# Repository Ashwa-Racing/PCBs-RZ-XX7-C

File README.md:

# RZ-XX7-C Electrical and PCB Designs

This repository contains the electrical design files for the Ashwa Racing
RZ-XX7-C, a 2027 combustion prototype. It covers the accelerator pedal position
sensor board (APPS), brake system plausibility device (BSPD), control unit,
interface control unit (ICU), and vehicle wiring harness.

The KiCad projects are the editable design sources. PDF drawings, PCB
manufacturing exports, and 3D models are included where available. Firmware
source and release binaries are not part of this repository.

## Design overview

| Design | Role |
| --- | --- |
| [APPS board](<./APPS-RZ-XX7-C/>) | Reads accelerator-pedal and throttle-position signals. Its schematic includes an STM32F4x1 module, analog signal conditioning, plausibility logic, relay control, and ETB-related signals. |
| [BSPD](<./BSPD-RZ-XX7-C/>) | Monitors brake-pressure, throttle-position, and brake-light-related signals. The schematic documents the plausibility, timing, reset, relay, and shutdown-circuit logic. |
| [Control Unit](<./Control Unit/>) | Provides power switching and control interfaces for the starter relay, fuel pump, electronic throttle body, radiator fan, water pump, and compressor. |
| [Interface Control Unit](<./Interface Control Unit/>) | Provides the vehicle interface electronics, including a Raspberry Pi Zero 2 W, CAN-FD controller and transceiver, IMU connections, and power/control circuitry for the display and auxiliary lighting. |
| [Harness](<./Harness-RZ-XX7-C/>) | Documents vehicle wiring and connectors between the engine-management system, boards, sensors, actuators, display, and vehicle systems. |

These descriptions summarize the design files; consult the schematics and
harness drawing for pin assignments, circuit details, and connector wiring.

## Repository contents

Each board folder contains a KiCad schematic (`.kicad_sch`), PCB layout
(`.kicad_pcb`), project settings (`.kicad_pro`), and a plotted schematic PDF.
The harness folder contains the corresponding wiring schematic, PCB document,
and PDF drawing.

| Folder | Design documents | Additional files |
| --- | --- | --- |
| [APPS-RZ-XX7-C](<./APPS-RZ-XX7-C/>) | [Schematic PDF](<./APPS-RZ-XX7-C/APPS-RZ-XX7-C%20Schematic%20PDF.pdf>) | [Gerbers and drill file](<./APPS-RZ-XX7-C/Gerbers/>), [3D model](<./APPS-RZ-XX7-C/APPS-RZ-XX7-C.step>) |
| [BSPD-RZ-XX7-C](<./BSPD-RZ-XX7-C/>) | [Schematic PDF](<./BSPD-RZ-XX7-C/BSPD-RZ-XX7-C%20Schematic%20PDF.pdf>) | [Gerbers and drill file](<./BSPD-RZ-XX7-C/Gerbers/>), [3D model](<./BSPD-RZ-XX7-C/BSPD-RZ-XX7-C.step>) |
| [Control Unit](<./Control Unit/>) | [Schematic PDF](<./Control%20Unit/Control%20Unit%20Schematic%20PDF.pdf>) | [Gerbers and drill file](<./Control%20Unit/Gerbers/>), [3D model](<./Control%20Unit/Control%20Unit.step>) |
| [Interface Control Unit](<./Interface Control Unit/>) | [Schematic PDF](<./Interface%20Control%20Unit/Interface%20Control%20Unit%20Schematic%20PDF.pdf>) | [Gerbers and drill file](<./Interface%20Control%20Unit/Gerbers/>), [ICU and display STEP archive](<./Interface%20Control%20Unit/ICU%20+%20Display%20V2%20STEP.zip>), [ICU STEP archive](<./Interface%20Control%20Unit/RZ-XX7-C%20ICU%20STEP.zip>) |
| [Harness-RZ-XX7-C](<./Harness-RZ-XX7-C/>) | [Harness PDF](<./Harness-RZ-XX7-C/Harness-RZ-XX7-C%20PDF.pdf>) | Reference manuals and wiring diagrams are in [Datasheets](<./Harness-RZ-XX7-C/Datasheets/>) |

The Gerber folders contain the copper, solder-mask, paste, silkscreen, and
board-outline layers, along with Excellon drill data. A Gerber set is currently
present for APPS, BSPD, Control Unit, and ICU; no harness Gerber export is
included.

The ICU folder also contains power-supply analysis documents in `Documents/`
and local KiCad symbol and footprint libraries alongside several projects.
Keep those libraries with their projects when moving or editing the designs;
KiCad may need their library paths configured on another machine.

## Opening and using the designs

1. Install KiCad and open a project's `.kicad_pro` file, or open its schematic
   or PCB file directly.
2. If KiCad reports missing symbols or footprints, configure the project's
   local libraries. Several custom libraries are stored in the relevant
   project folders.
3. Review the schematic and PCB together before making changes. Use the
   checked-in PDFs for quick reference; the KiCad files remain the editable
   source.
4. For fabrication, review the Gerber and drill files in a Gerber viewer and
   confirm the board revision and fabrication requirements before sending
   them to a manufacturer. Regenerate the exports from the KiCad source after
   changing a design.

The Gerber file headers identify KiCad 10.0.6 as the export version. KiCad
projects and generated manufacturing files should be checked together when
preparing a new release.

## Firmware status

- [ ] Upload the updated firmware to the target hardware.

Firmware source and binaries are not stored here, so this repository does not
provide firmware build or upload instructions.

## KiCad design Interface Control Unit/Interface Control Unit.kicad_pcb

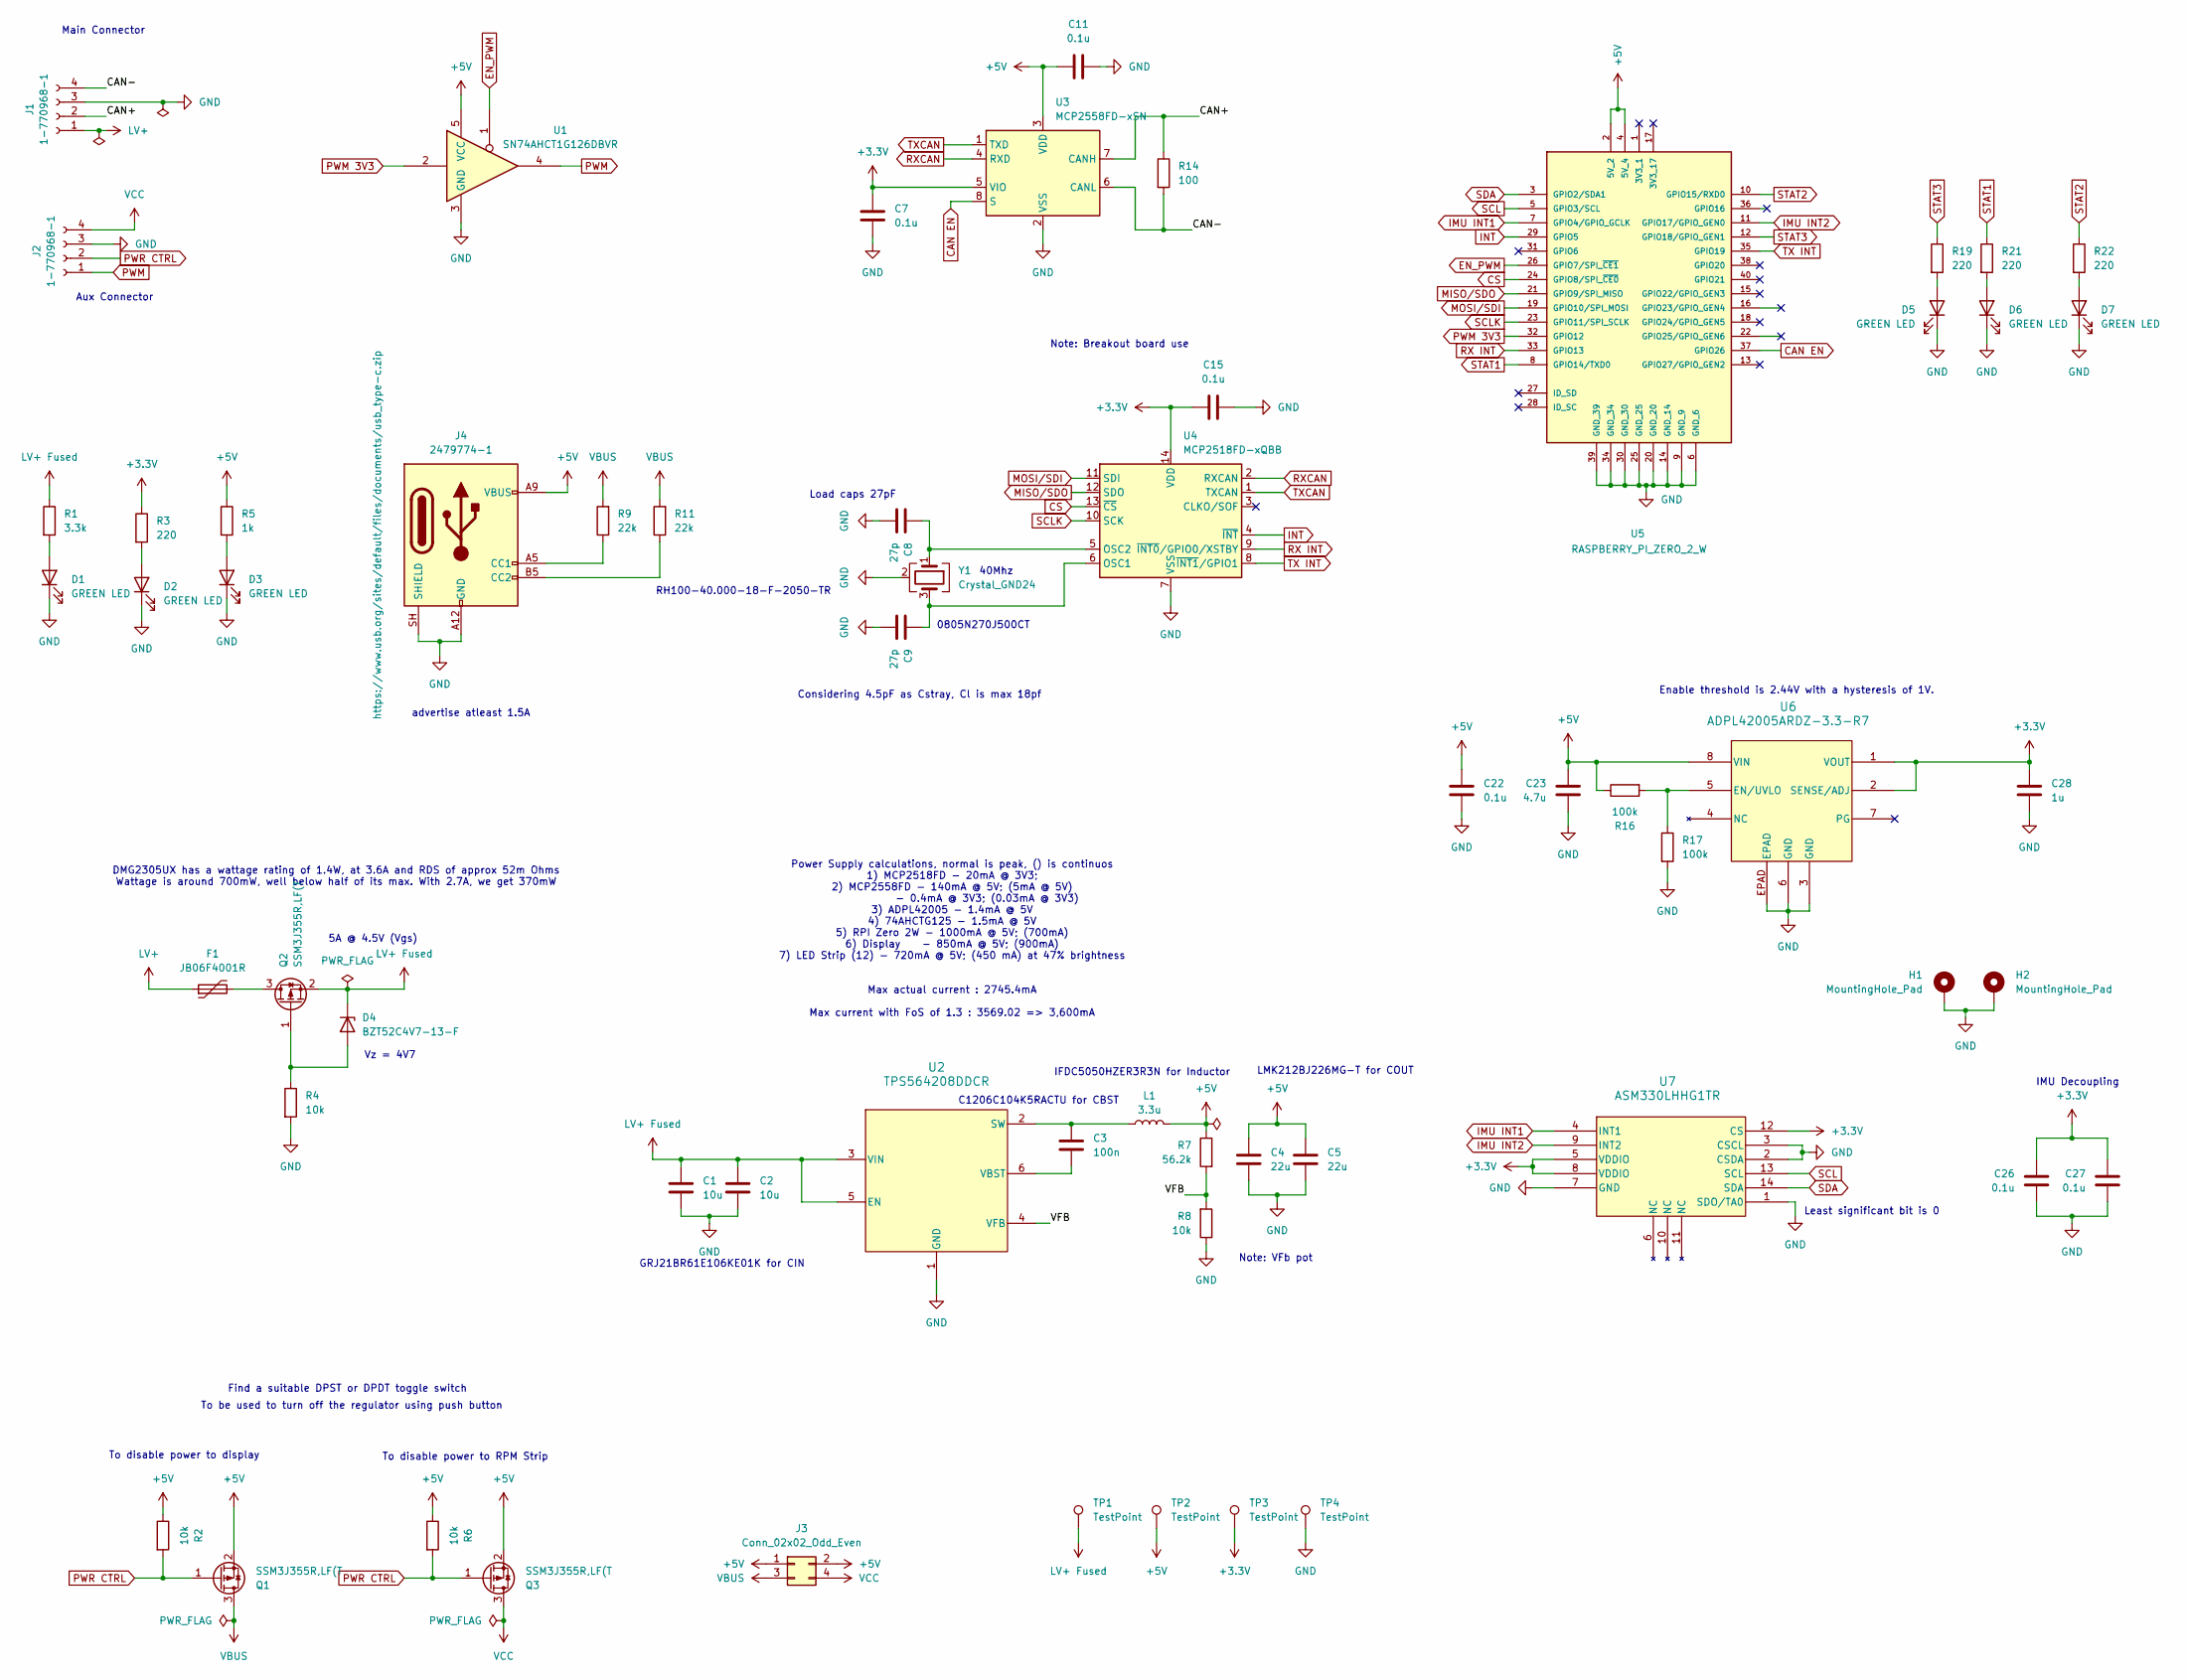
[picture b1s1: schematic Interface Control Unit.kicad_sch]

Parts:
C1, C2: 10u; C_0805_2012Metric_Pad1.18x1.45mm_HandSolder
C3: 100n; C_1206_3216Metric_Pad1.33x1.80mm_HandSolder
C4, C5: 22u; C_0805_2012Metric_Pad1.18x1.45mm_HandSolder
C7, C11, C15, C22, C26, C27: 0.1u; C_1206_3216Metric_Pad1.33x1.80mm_HandSolder
C8, C9: 27p; C_0805_2012Metric_Pad1.18x1.45mm_HandSolder
C23: 4.7u; C_1206_3216Metric_Pad1.33x1.80mm_HandSolder
C28: 1u; C_1206_3216Metric_Pad1.33x1.80mm_HandSolder
D1, D2, D3, D5, D6, D7: GREEN LED; LED_1206_3216Metric_Pad1.42x1.75mm_HandSolder
D4: BZT52C4V7-13-F; D_SOD-123F
F1: JB06F4001R; Fuse_0603_1608Metric_Pad1.05x0.95mm_HandSolder
H1, H2: MountingHole_Pad; MountingHole_2.7mm_M2.5_ISO7380_Pad
J1, J2: 1-770968-1; CONN4_1-770968-1_TEC
J3: Conn_02x02_Odd_Even; PinHeader_2x02_P2.54mm_Vertical
J4: 2479774-1; USB_C_Receptacle_GCT_USB4125-xx-x-0190_6P_TopMnt_Horizontal
L1: 3.3u; L_Vishay_IHLP-5050
Q1, Q2, Q3: SSM3J355R,LF(T; SOTFL95P240X88-3N
R1: 3.3k; R_1206_3216Metric_Pad1.30x1.75mm_HandSolder
R2, R4, R6: 10k; R_1206_3216Metric_Pad1.30x1.75mm_HandSolder
R3, R19, R21, R22: 220; R_1206_3216Metric_Pad1.30x1.75mm_HandSolder
R5: 1k; R_1206_3216Metric_Pad1.30x1.75mm_HandSolder
R7: 56.2k; R_0805_2012Metric_Pad1.20x1.40mm_HandSolder
R8: 10k; R_0805_2012Metric_Pad1.20x1.40mm_HandSolder
R9, R11: 22k; R_1206_3216Metric_Pad1.30x1.75mm_HandSolder
R14: 100; R_1206_3216Metric_Pad1.30x1.75mm_HandSolder
R16, R17: 100k; R_1206_3216Metric_Pad1.30x1.75mm_HandSolder
TP1, TP2, TP3, TP4: TestPoint; TestPoint_Pad_D2.0mm
U1: SN74AHCT1G126DBVR; SOT-23-5
U2: TPS564208DDCR; DDC0006A_M
U3: MCP2558FD-xSN; SOIC-8_3.9x4.9mm_P1.27mm
U4: MCP2518FD-xQBB; SOIC-14_3.9x8.7mm_P1.27mm
U5: RASPBERRY_PI_ZERO_2_W; Raspberry Pi Zero 2WH; PARTREV April 2024
U6: ADPL42005ARDZ-3.3-R7; RD-8-1_ADI-M
U7: ASM330LHHG1TR; LGA14L_2P5X3_STM-M
Y1: Crystal_GND24; Crystal_SMD_3225-4Pin_3.2x2.5mm

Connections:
+3.3V: C7.1, C15.1, C26.1, C27.1, C28.1, R3.1, TP3.1 (1_1), U3.5 (VIO), U4.14 (VDD), U6.1 (VOUT), U6.2 (SENSE/ADJ), U7.5 (VDDIO), U7.8 (VDDIO), U7.12 (CS)
+5V: C4.1, C5.1, C11.1, C22.1, C23.1, J3.1, J3.2, J4.A9 (VBUS), J4.B9 (VBUS), L1.2, Q1.2 (S), Q3.2 (S), R2.1, R5.1, R6.1, R7.1, R16.1, TP2.1 (1_1), U1.5 (VCC), U3.3 (VDD), U5.2 (5V_2), U5.4 (5V_4), U6.8 (VIN)
/CAN+: J1.2, R14.1, U3.7 (CANH)
/CAN-: J1.4, R14.2, U3.6 (CANL)
/VFB: R7.2, R8.2, U2.4 (VFB)
CAN EN: U3.8 (S), U5.37 (GPIO26)
CS: U4.13 (~CS), U5.24 (GPIO8/SPI_~CE0)
EN_PWM: U1.1, U5.26 (GPIO7/SPI_~CE1)
GND: C1.2, C2.2, C4.2, C5.2, C7.2, C8.2, C9.2, C11.2, C15.2, C22.2, C23.2, C26.2, C27.2, C28.2, D1.1 (K), D2.1 (K), D3.1 (K), D5.1 (K), D6.1 (K), D7.1 (K), H1.1 (1_1), H2.1 (1_1), J1.3, J2.3, J4.A12 (GND), J4.B12 (GND), J4.SH (SHIELD), R4.2, R8.1, R17.2, TP4.1 (1_1), U1.3 (GND), U2.1 (GND), U3.2 (VSS), U4.7 (VSS), U4.15 (VSS), U5.6 (GND_6), U5.9 (GND_9), U5.14 (GND_14), U5.20 (GND_20), U5.25 (GND_25), U5.30 (GND_30), U5.34 (GND_34), U5.39 (GND_39), U6.3 (GND), U6.6 (GND), U6.EPAD, U7.1 (SDO/TA0), U7.2 (CSDA), U7.3 (CSCL), U7.7 (GND), Y1.2 (G), Y1.4 (G)
IMU INT1: U5.7 (GPIO4/GPIO_GCLK), U7.4 (INT1)
IMU INT2: U5.11 (GPIO17/GPIO_GEN0), U7.9 (INT2)
INT: U4.4 (~INT), U5.29 (GPIO5)
LV+: F1.1, J1.1
LV+ Fused: C1.1, C2.1, D4.1 (K), Q2.2 (S), R1.1, TP1.1 (1_1), U2.3 (VIN), U2.5 (EN)
MISO/SDO: U4.12 (SDO), U5.21 (GPIO9/SPI_MISO)
MOSI/SDI: U4.11 (SDI), U5.19 (GPIO10/SPI_MOSI)
unnamed: D1.2 (A), R1.2
unnamed: D2.2 (A), R3.2
unnamed: D3.2 (A), R5.2
unnamed: D4.2 (A), Q2.1 (G), R4.1
unnamed: D5.2 (A), R19.2
unnamed: D6.2 (A), R21.2
unnamed: D7.2 (A), R22.2
unnamed: J4.A5 (CC1), R9.1
unnamed: J4.B5 (CC2), R11.1
unnamed: F1.2, Q2.3 (D)
unnamed: C3.1, L1.1, U2.2 (SW)
unnamed: C3.2, U2.6 (VBST)
unnamed: C9.1, U4.6 (OSC1), Y1.3
unnamed: C8.1, U4.5 (OSC2), Y1.1
unnamed: R16.2, R17.1, U6.5 (EN/UVLO)
PWM: J2.1, U1.4
PWM 3V3: U1.2, U5.32 (GPIO12)
PWR CTRL: J2.2, Q1.1 (G), Q3.1 (G), R2.2, R6.2
RX INT: U4.9 (~INT0/GPIO0/XSTBY), U5.33 (GPIO13)
RXCAN: U3.4 (RXD), U4.2 (RXCAN)
SCL: U5.5 (GPIO3/SCL), U7.13 (SCL)
SCLK: U4.10 (SCK), U5.23 (GPIO11/SPI_SCLK)
SDA: U5.3 (GPIO2/SDA1), U7.14 (SDA)
STAT1: R21.1, U5.8 (GPIO14/TXD0)
STAT2: R22.1, U5.10 (GPIO15/RXD0)
STAT3: R19.1, U5.12 (GPIO18/GPIO_GEN1)
TX INT: U4.8 (~INT1/GPIO1), U5.35 (GPIO19)
TXCAN: U3.1 (TXD), U4.1 (TXCAN)
VBUS: J3.3, Q1.3 (D), R9.2, R11.2
VCC: J2.4, J3.4, Q3.3 (D)

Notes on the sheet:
Enable threshold is 2.44V with a hysteresis of 1V.
IFDC5050HZER3R3N for Inductor
Power Supply calculations, normal is peak, () is continuos 1) MCP2518FD - 20mA @ 3V3; 2) MCP2558FD - 140mA @ 5V; (5mA @ 5V) - 0.4mA @ 3V3; (0.03mA @ 3V3) 3) ADPL42005 - 1.4mA @ 5V 4) 74AHCTG125 - 1.5mA @ 5V 5) RPI Zero 2W - 1000mA @ 5V; (700mA) 6) Display - 850mA @ 5V; (900mA) 7) LED Strip (12) - 7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
To disable power to display
To be used to turn off the regulator using push button
0805N270J500CT
Considering 4.5pF as Cstray, Cl is max 18pf
Main Connector
40Mhz
Note: Breakout board use
Load caps 27pF
Note: VFb pot
C1206C104K5RACTU for CBST
Least significant bit is 0
advertise atleast 1.5A
To disable power to RPM Strip
Aux Connector
LMK212BJ226MG-T for COUT
DMG2305UX has a wattage rating of 1.4W, at 3.6A and RDS of approx 52m Ohms Wattage is around 700mW, well below half of its max. With 2.7A, we get 370mW
IMU Decoupling
5A @ 4.5V (Vgs)
RH100-40.000-18-F-2050-TR
GRJ21BR61E106KE01K for CIN
Find a suitable DPST or DPDT toggle switch
Vz = 4V7

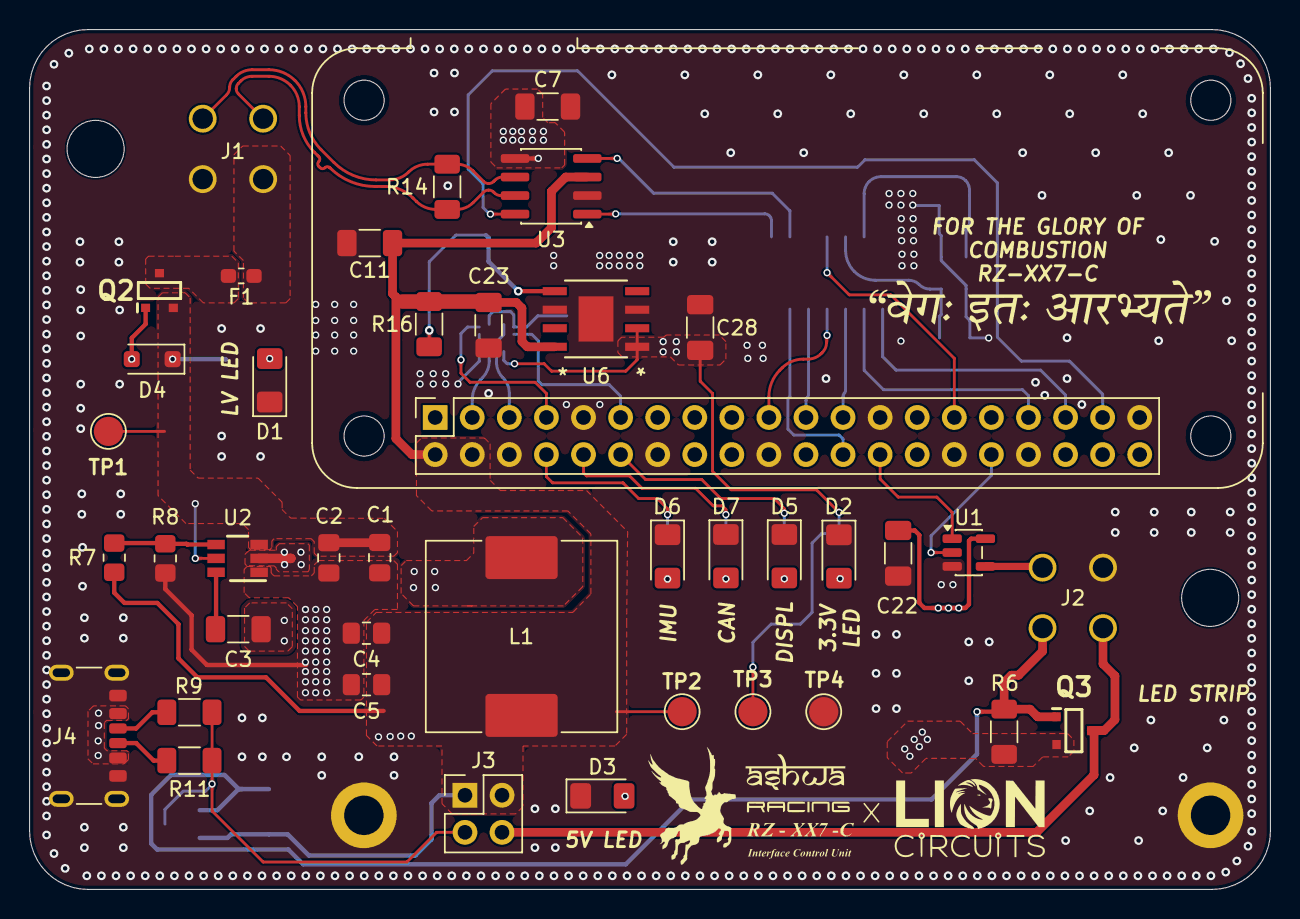
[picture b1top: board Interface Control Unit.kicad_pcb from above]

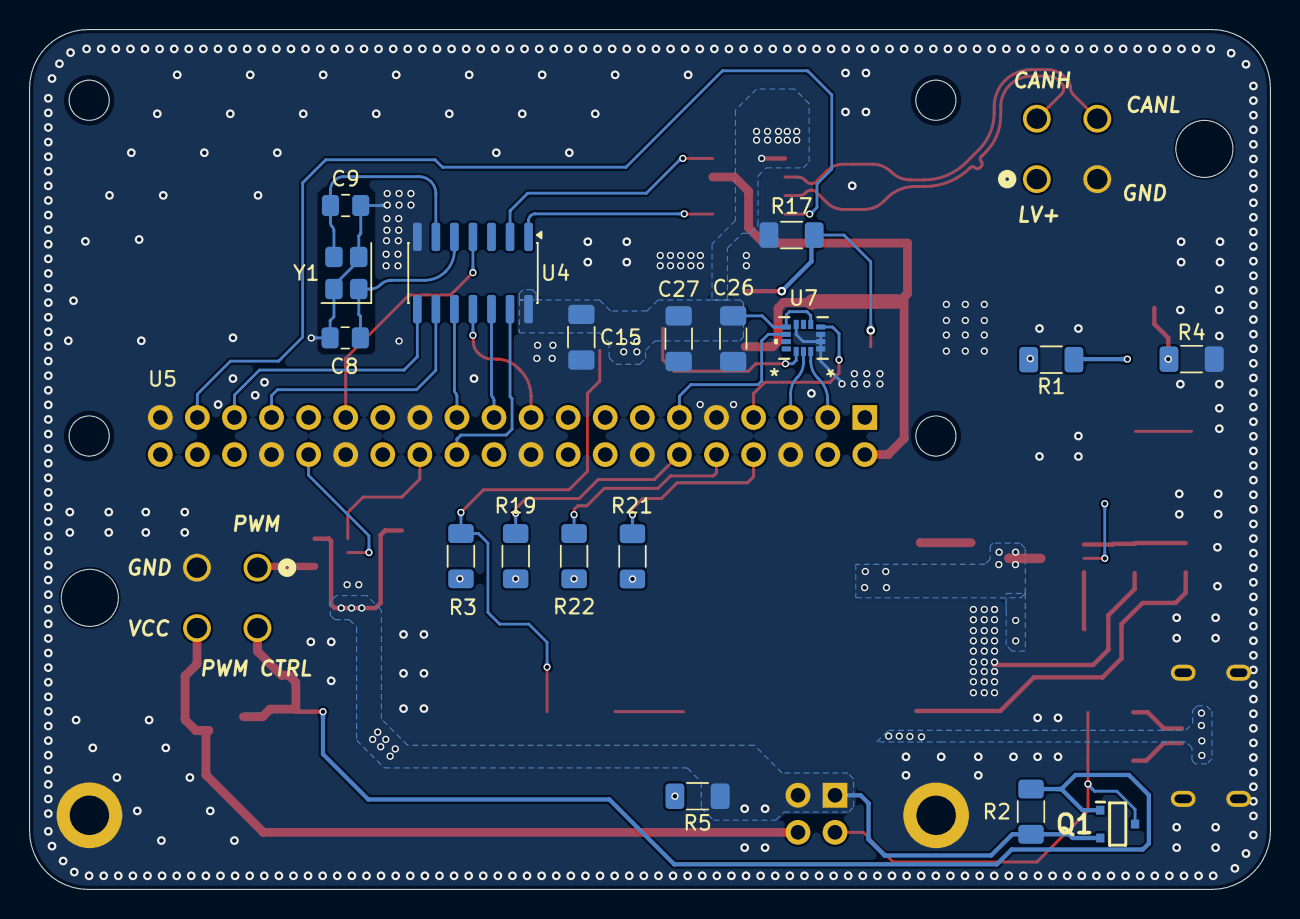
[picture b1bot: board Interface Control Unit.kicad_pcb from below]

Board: 2 copper layers, 85.0 x 58.9 mm, 61 parts (18 on the bottom side), 46 nets.

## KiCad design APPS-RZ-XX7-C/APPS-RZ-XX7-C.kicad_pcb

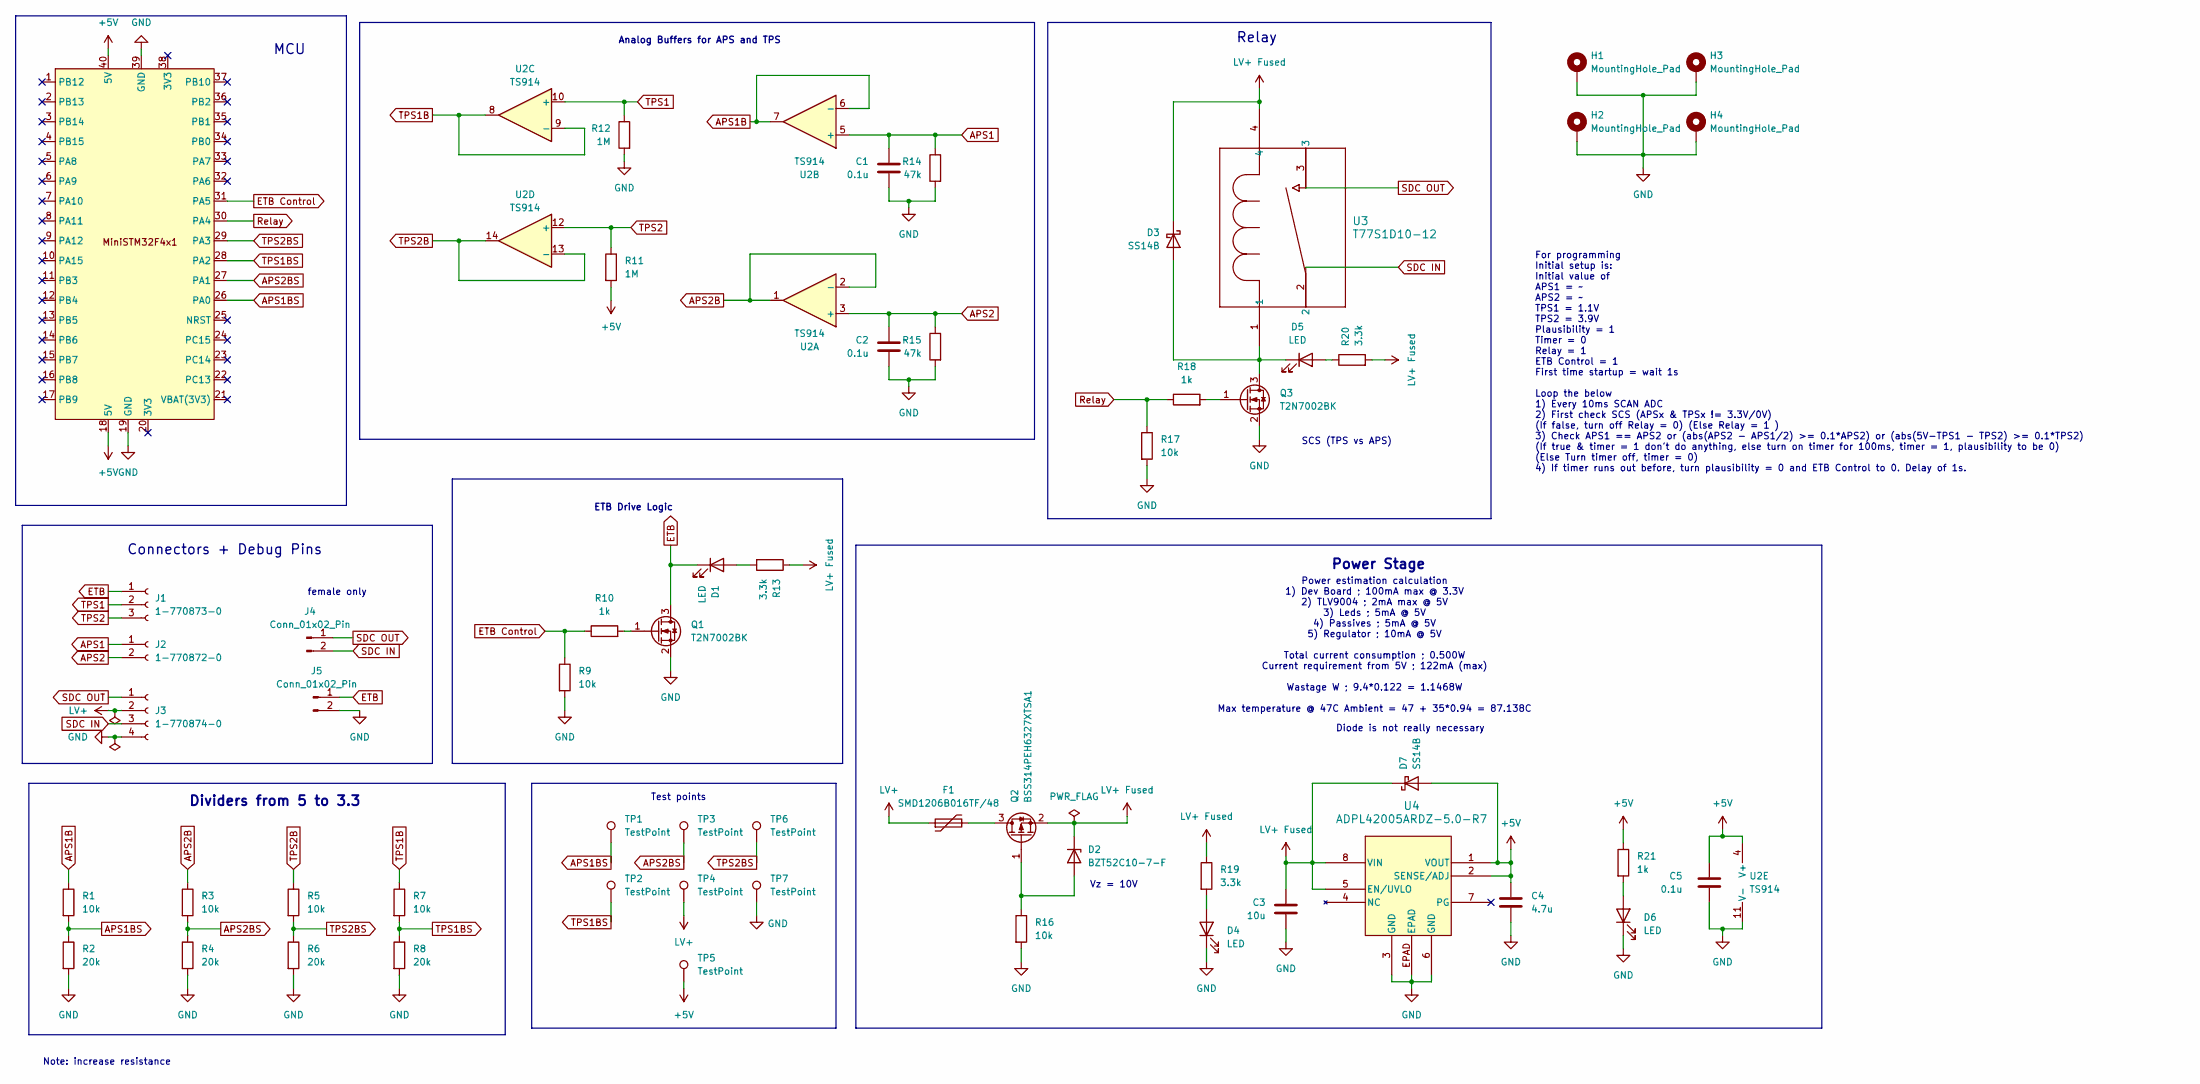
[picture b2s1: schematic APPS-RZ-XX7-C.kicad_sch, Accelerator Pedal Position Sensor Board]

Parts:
C1, C2, C5: 0.1u; C_1206_3216Metric_Pad1.33x1.80mm_HandSolder
C3: 10u; C_1206_3216Metric_Pad1.33x1.80mm_HandSolder
C4: 4.7u; C_1206_3216Metric_Pad1.33x1.80mm_HandSolder
D1, D4, D5, D6: LED; LED_1206_3216Metric_Pad1.42x1.75mm_HandSolder
D2: BZT52C10-7-F; D_SOD-123F
D3, D7: SS14B; D_SMB
F1: SMD1206B016TF/48; Fuse_1206_3216Metric_Pad1.42x1.75mm_HandSolder
H1, H2, H3, H4: MountingHole_Pad; MountingHole_4.3mm_M4_ISO7380_Pad
J1: 1-770873-0; CON3_1X3_P163_VMNL-1MTG_TYC
J2: 1-770872-0; CON2_1X2_P163_VMNL-1MTG_TYC
J3: 1-770874-0; CONN4_1-770874-0_TEC
J4, J5: Conn_01x02_Pin; PinHeader_1x02_P2.54mm_Vertical
Q1, Q3: T2N7002BK; SOT-23
Q2: BSS314PEH6327XTSA1; SOT-23
R1, R3, R5, R7, R9, R16, R17: 10k; R_1206_3216Metric_Pad1.30x1.75mm_HandSolder
R2, R4, R6, R8: 20k; R_1206_3216Metric_Pad1.30x1.75mm_HandSolder
R10, R18, R21: 1k; R_1206_3216Metric_Pad1.30x1.75mm_HandSolder
R11, R12: 1M; R_1206_3216Metric_Pad1.30x1.75mm_HandSolder
R13, R19, R20: 3.3k; R_1206_3216Metric_Pad1.30x1.75mm_HandSolder
R14, R15: 47k; R_1206_3216Metric_Pad1.30x1.75mm_HandSolder
TP1, TP2, TP3, TP4, TP5, TP6, TP7: TestPoint; TestPoint_Pad_D2.0mm
U1: MiniSTM32F4x1; Mini_F4X1_STM32
U2: TS914; SOIC-14_3.9x8.7mm_P1.27mm
U3: T77S1D10-12; RELAY4-402X717_575
U4: ADPL42005ARDZ-5.0-R7; RD-8-1_ADI

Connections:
+5V: C4.1, C5.1, D7.2 (A), R11.2, R21.1, TP5.1 (1_1), U1.18 (5V), U1.40 (5V), U2.4 (V+), U4.1 (VOUT), U4.2 (SENSE/ADJ)
APS1: C1.1, J2.1, R14.1, U2.5 (+)
APS1B: R1.1, U2.6 (-), U2.7
APS1BS: R1.2, R2.1, TP1.1 (1_1), U1.26 (PA0)
APS2: C2.1, J2.2, R15.1, U2.3 (+)
APS2B: R3.1, U2.1, U2.2 (-)
APS2BS: R3.2, R4.1, TP3.1 (1_1), U1.27 (PA1)
ETB: D1.1 (K), J1.1, J5.1, Q1.3 (D)
ETB Control: R9.1, R10.1, U1.31 (PA5)
GND: C1.2, C2.2, C3.2, C4.2, C5.2, D4.1 (K), D6.1 (K), H1.1 (1_1), H2.1 (1_1), H3.1 (1_1), H4.1 (1_1), J3.4, J5.2, Q1.2 (S), Q3.2 (S), R2.2, R4.2, R6.2, R8.2, R9.2, R12.2, R14.2, R15.2, R16.2, R17.2, TP7.1 (1_1), U1.19 (GND), U1.39 (GND), U2.11 (V-), U4.3 (GND), U4.6 (GND), U4.EPAD
LV+: F1.1, J3.2, TP4.1 (1_1)
LV+ Fused: C3.1, D2.1 (K), D3.1 (K), D7.1 (K), Q2.2 (S), R13.1, R19.1, R20.2, U3.4, U4.5 (EN/UVLO), U4.8 (VIN)
unnamed: D1.2 (A), R13.2
unnamed: D2.2 (A), Q2.1 (G), R16.1
unnamed: D3.2 (A), D5.1 (K), Q3.3 (D), U3.1
unnamed: D4.2 (A), R19.2
unnamed: D5.2 (A), R20.1
unnamed: D6.2 (A), R21.2
unnamed: Q1.1 (G), R10.2
unnamed: F1.2, Q2.3 (D)
unnamed: Q3.1 (G), R18.2
Relay: R17.1, R18.1, U1.30 (PA4)
SDC IN: J3.3, J4.2, U3.2
SDC OUT: J3.1, J4.1, U3.3
TPS1: J1.2, R12.1, U2.10 (+)
TPS1B: R7.1, U2.8, U2.9 (-)
TPS1BS: R7.2, R8.1, TP2.1 (1_1), U1.28 (PA2)
TPS2: J1.3, R11.1, U2.12 (+)
TPS2B: R5.1, U2.13 (-), U2.14
TPS2BS: R5.2, R6.1, TP6.1 (1_1), U1.29 (PA3)

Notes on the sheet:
female only
For programming Initial setup is: Initial value of APS1 = ~ APS2 = ~ TPS1 = 1.1V TPS2 = 3.9V Plausibility = 1 Timer = 0 Relay = 1 ETB Control = 1 First time startup = wait 1s Loop the below 1) Every 10ms SCAN ADC 2) First check SCS (APSx & TPSx != 3.3V/0V) (If false, turn off Relay = 0) (Else Relay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
Relay
Power Stage
Note: increase resistance
SCS (TPS vs APS)
MCU
Vz = 10V
Connectors + Debug Pins
Dividers from 5 to 3.3
Test points
Power estimation calculation 1) Dev Board ; 100mA max @ 3.3V 2) TLV9004 ; 2mA max @ 5V 3) Leds ; 5mA @ 5V 4) Passives ; 5mA @ 5V 5) Regulator ; 10mA @ 5V Total current consumption ; 0.500W Current requirement from 5V ; 122mA (max) Wastage W ; 9.4*0.122 = 1.1468W Max temperature @ 47C Ambient = 47 +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
ETB Drive Logic
Analog Buffers for APS and TPS
Diode is not really necessary

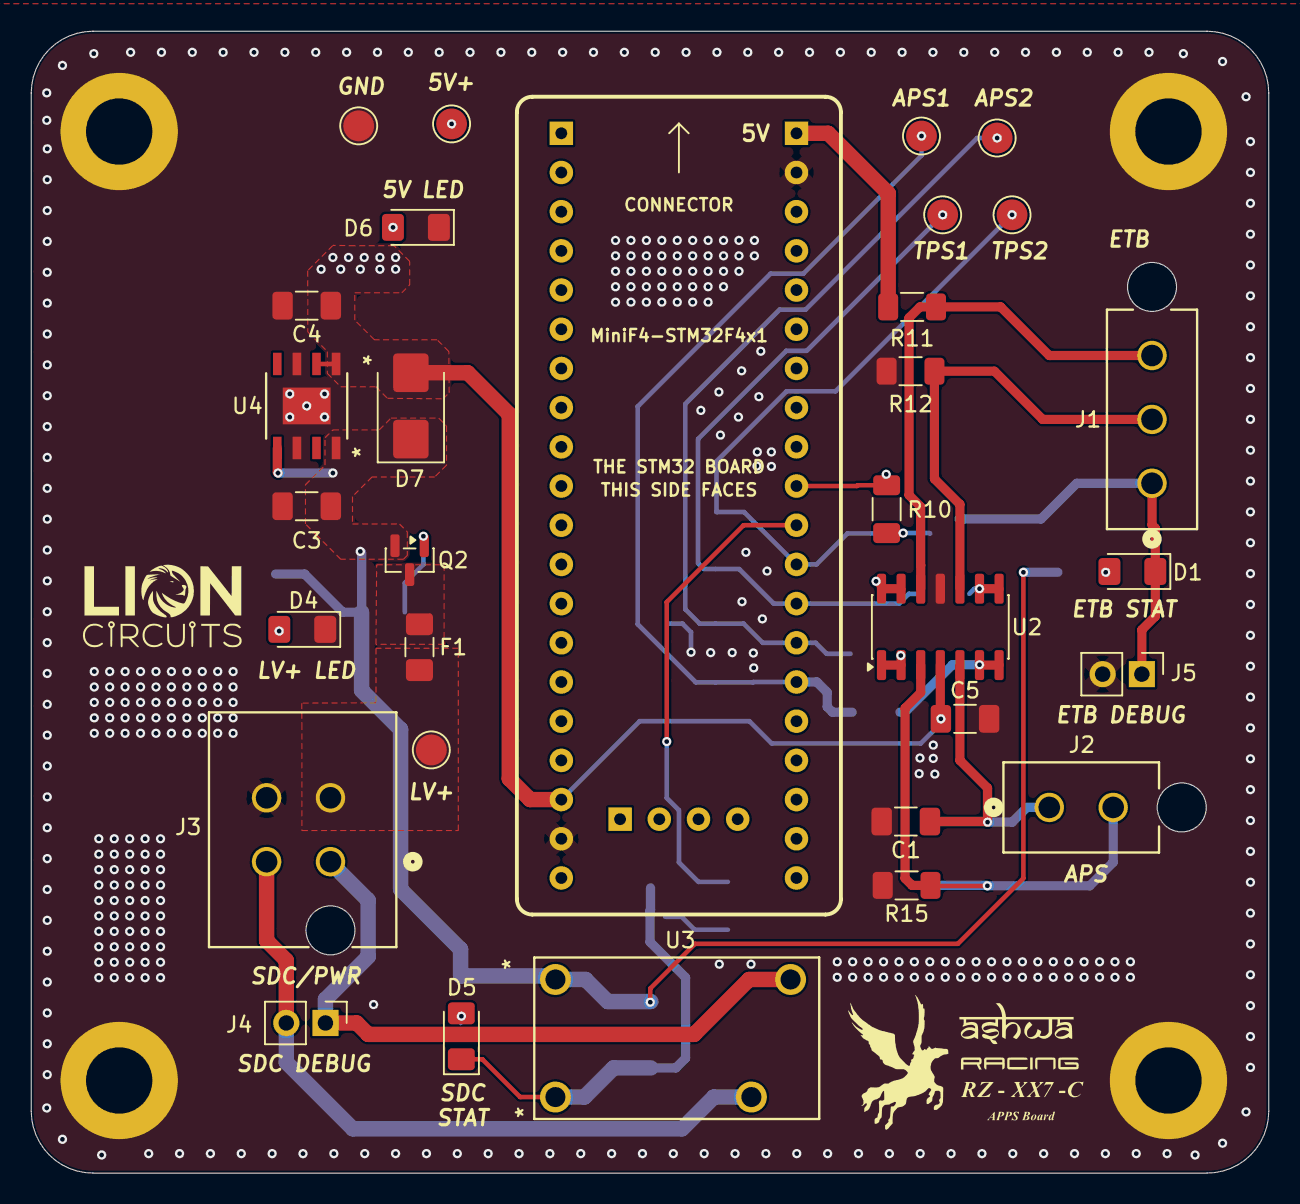
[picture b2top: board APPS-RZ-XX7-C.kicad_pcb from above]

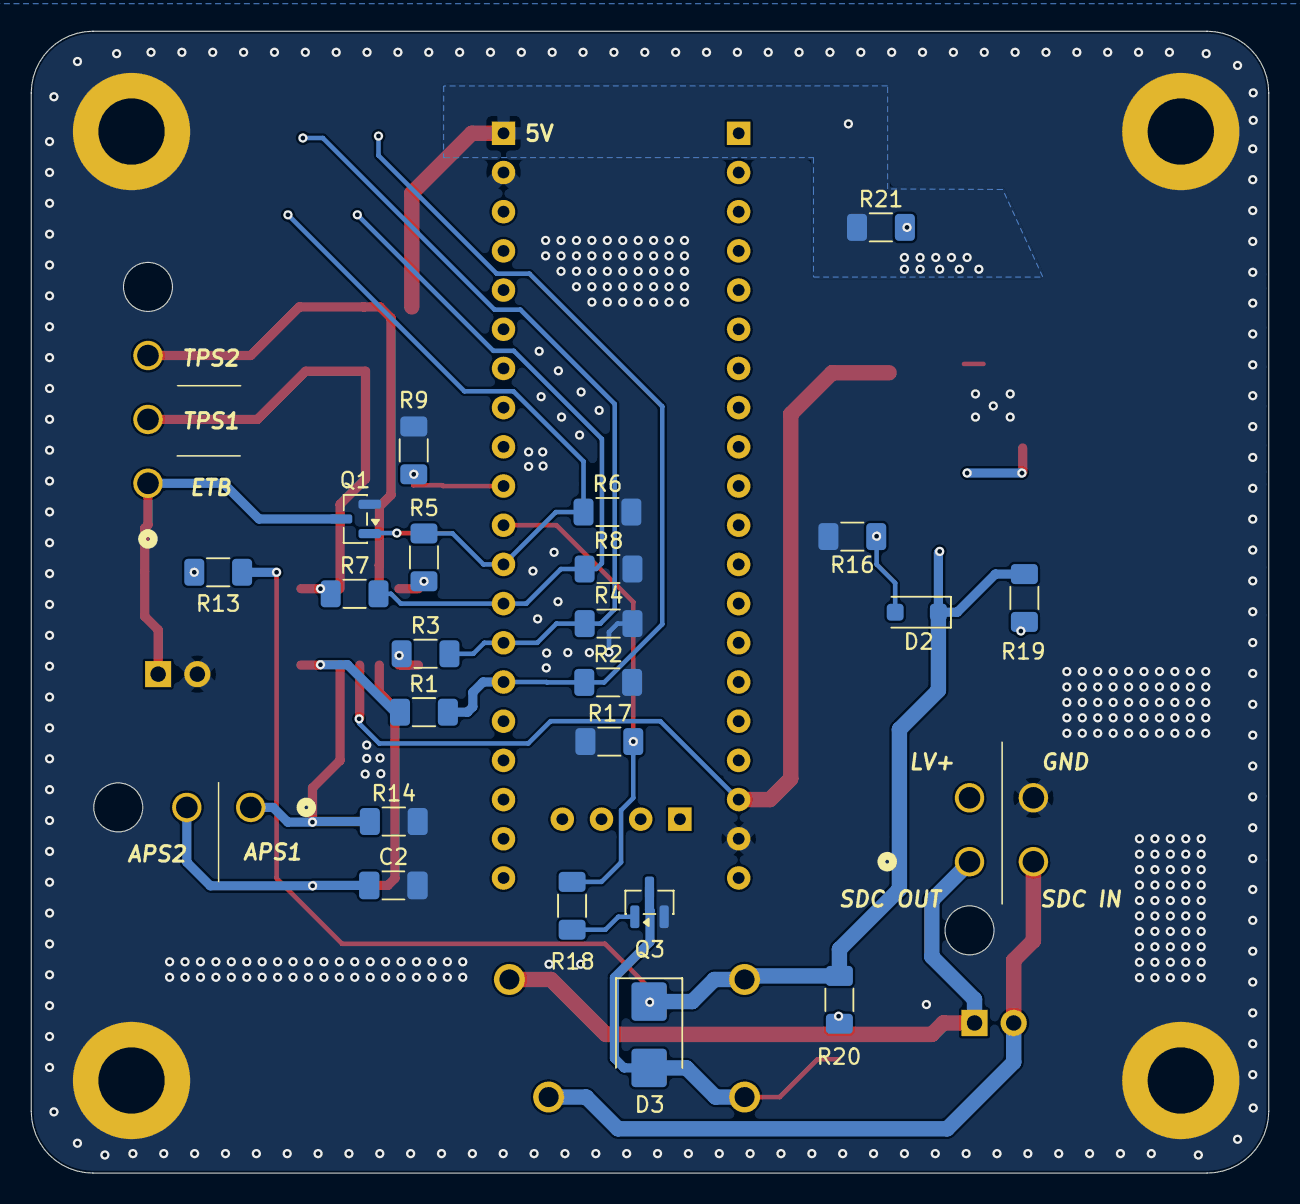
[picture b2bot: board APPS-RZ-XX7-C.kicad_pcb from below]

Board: 2 copper layers, 80.2 x 74.0 mm, 57 parts (22 on the bottom side), 30 nets.

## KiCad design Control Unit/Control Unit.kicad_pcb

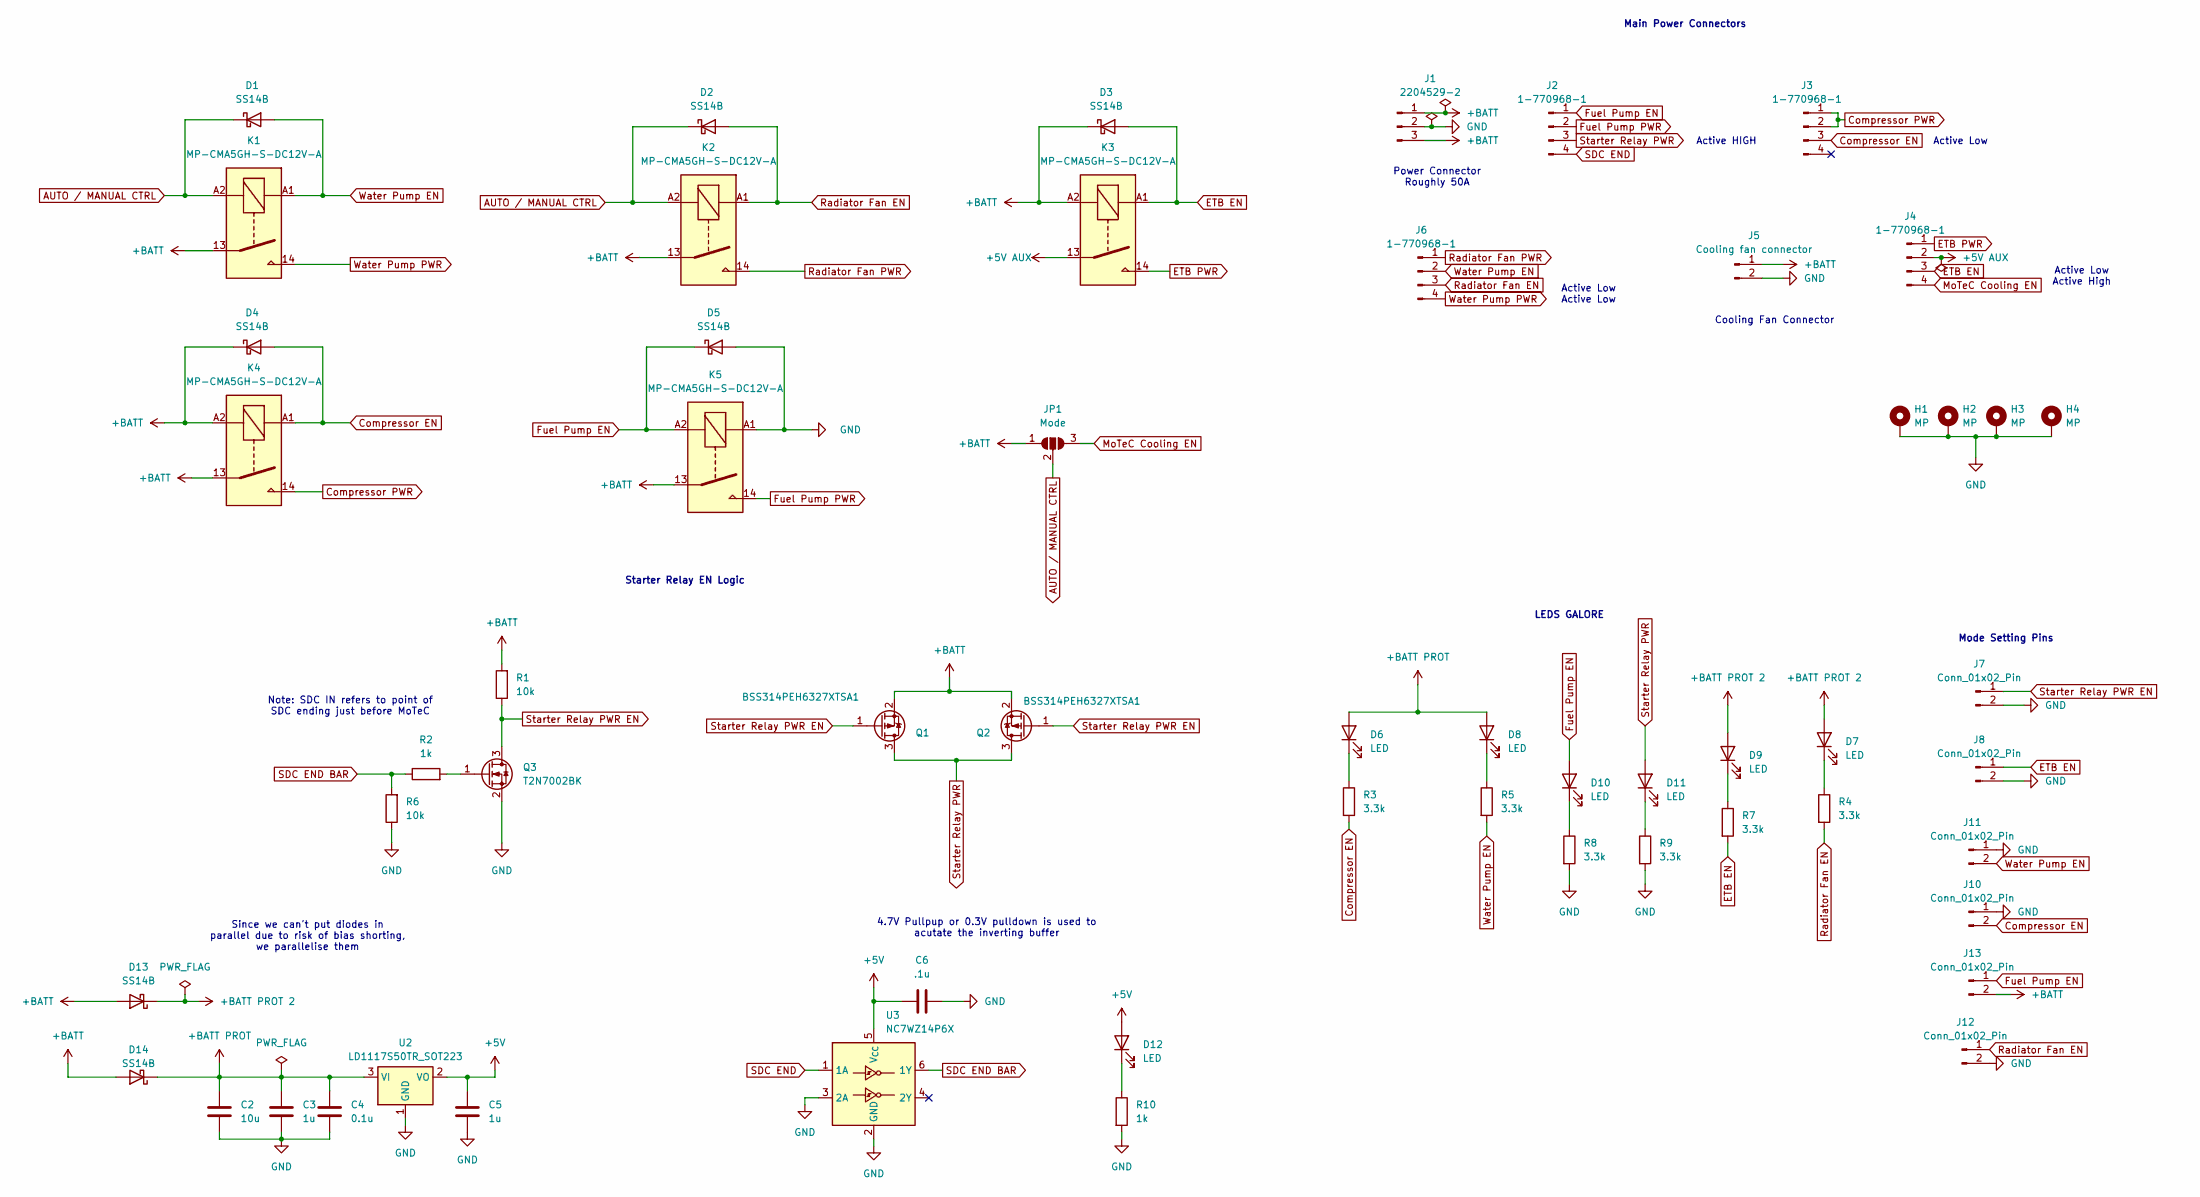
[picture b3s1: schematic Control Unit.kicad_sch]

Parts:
C2: 10u; C_1206_3216Metric_Pad1.33x1.80mm_HandSolder
C3, C5: 1u; C_1206_3216Metric_Pad1.33x1.80mm_HandSolder
C4: 0.1u; C_1206_3216Metric_Pad1.33x1.80mm_HandSolder
C6: .1u; C_1206_3216Metric_Pad1.33x1.80mm_HandSolder
D1, D2, D3, D4, D5, D13, D14: SS14B; D_SMB
D6, D7, D8, D9, D10, D11, D12: LED; LED_1206_3216Metric_Pad1.42x1.75mm_HandSolder
H1, H2, H3, H4: MP; MountingHole_4.3mm_M4_ISO7380_Pad
J1: 2204529-2
J2, J3, J4, J6: 1-770968-1; CONN4_1-770968-1_TEC
J5: Cooling fan connector; JST_XH_B2B-XH-A_1x02_P2.50mm_Vertical
J7, J8, J10, J11, J12, J13: Conn_01x02_Pin; PinSocket_1x02_P2.54mm_Vertical
JP1: Mode; SolderJumper-3_P1.3mm_Open_RoundedPad1.0x1.5mm
K1, K2, K3, K4, K5: MP-CMA5GH-S-DC12V-A; MPCMA5GHSDC12VA
Q1, Q2: BSS314PEH6327XTSA1; SOT-23
Q3: T2N7002BK; SOT-23
R1, R6: 10k; R_1206_3216Metric_Pad1.30x1.75mm_HandSolder
R2, R10: 1k; R_1206_3216Metric_Pad1.30x1.75mm_HandSolder
R3, R4, R5, R7, R8, R9: 3.3k; R_1206_3216Metric_Pad1.30x1.75mm_HandSolder
U2: LD1117S50TR_SOT223; SOT-223-3_TabPin2
U3: NC7WZ14P6X; SOT-363_SC-70-6

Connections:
+5V: C5.1, C6.1, D12.2 (A), U2.2 (VO), U3.5 (V_{CC})
+5V AUX: J4.2, K3.13
+BATT: D3.1 (K), D4.1 (K), D13.2 (A), D14.2 (A), J1.1, J1.3, J5.1, J13.2, JP1.1 (A), K1.13, K2.13, K3.A2, K4.13, K4.A2, K5.13, Q1.2 (S), Q2.2 (S), R1.2
+BATT PROT: C2.1, C3.1, C4.1, D6.2 (A), D8.2 (A), D14.1 (K), U2.3 (VI)
+BATT PROT 2: D7.2 (A), D9.2 (A), D13.1 (K)
AUTO / MANUAL CTRL: D1.1 (K), D2.1 (K), JP1.2 (C), K1.A2, K2.A2
Compressor EN: D4.2 (A), J3.3, J10.2, K4.A1, R3.2
Compressor PWR: J3.1, J3.2, K4.14
ETB EN: D3.2 (A), J4.3, J8.1, K3.A1, R7.2
ETB PWR: J4.1, K3.14
Fuel Pump EN: D5.1 (K), D10.2 (A), J2.1, J13.1, K5.A2
Fuel Pump PWR: J2.2, K5.14
GND: C2.2, C3.2, C4.2, C5.2, C6.2, D5.2 (A), H1.1 (1_1), H2.1 (1_1), H3.1 (1_1), H4.1 (1_1), J1.2, J5.2, J7.2, J8.2, J10.1, J11.1, J12.2, K5.A1, Q3.2 (S), R6.1, R8.2, R9.2, R10.2, U2.1 (GND), U3.2 (GND), U3.3 (2A)
MoTeC Cooling EN: J4.4, JP1.3 (B)
unnamed: D6.1 (K), R3.1
unnamed: D7.1 (K), R4.1
unnamed: D8.1 (K), R5.1
unnamed: D9.1 (K), R7.1
unnamed: D10.1 (K), R8.1
unnamed: D11.1 (K), R9.1
unnamed: D12.1 (K), R10.1
unnamed: Q3.1 (G), R2.2
Radiator Fan EN: D2.2 (A), J6.3, J12.1, K2.A1, R4.2
Radiator Fan PWR: J6.1, K2.14
SDC END: J2.4, U3.1 (1A)
SDC END BAR: R2.1, R6.2, U3.6 (1Y)
Starter Relay PWR: D11.2 (A), J2.3, Q1.3 (D), Q2.3 (D)
Starter Relay PWR EN: J7.1, Q1.1 (G), Q2.1 (G), Q3.3 (D), R1.1
Water Pump EN: D1.2 (A), J6.2, J11.2, K1.A1, R5.2
Water Pump PWR: J6.4, K1.14

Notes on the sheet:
Starter Relay EN Logic
4.7V Pullpup or 0.3V pulldown is used to acutate the inverting buffer
Active Low
LEDS GALORE
Main Power Connectors
Since we can't put diodes in parallel due to risk of bias shorting, we parallelise them
Note: SDC IN refers to point of SDC ending just before MoTeC
Mode Setting Pins
Active Low Active High
Power Connector Roughly 50A
Active HIGH
Cooling Fan Connector
Active Low Active Low
